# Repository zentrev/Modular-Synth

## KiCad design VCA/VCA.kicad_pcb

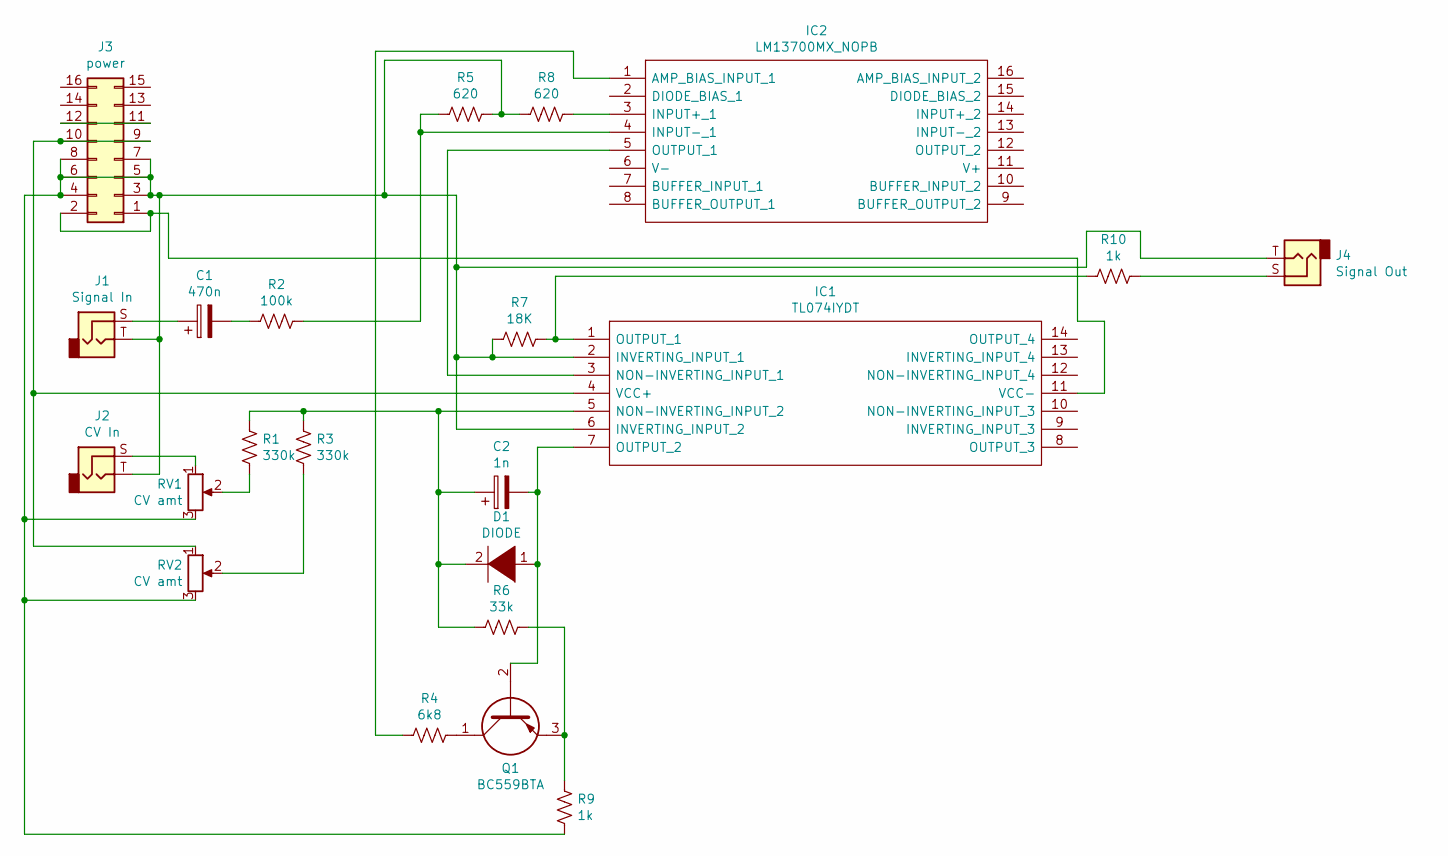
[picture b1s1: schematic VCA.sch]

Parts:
C1: 470n; CP_Radial_D4.0mm_P2.00mm
C2: 1n; CP_Radial_D4.0mm_P2.00mm
D1: DIODE; D_A-405_P2.54mm_Vertical_AnodeUp
IC1: TL074IYDT; SOIC127P600X175-14N; Mouser Part Number 511-TL074IYDT
IC2: LM13700MX_NOPB; SOIC127P600X175-16N; Mouser Part Number 926-LM13700MX/NOPB
J1: Signal In; Jack_3.5mm_CUI_SJ-3523-SMT_Horizontal
J2: CV In; Jack_3.5mm_CUI_SJ-3523-SMT_Horizontal
J3: power; IDC-Header_2x08_P2.54mm_Vertical
J4: Signal Out; Jack_3.5mm_CUI_SJ-3523-SMT_Horizontal
Q1: BC559BTA; TO-92_3L__AMMO_; Mouser Part Number 512-BC559BTA
R1, R3: 330k; R_Axial_DIN0204_L3.6mm_D1.6mm_P2.54mm_Vertical
R2: 100k; R_Axial_DIN0204_L3.6mm_D1.6mm_P2.54mm_Vertical
R4: 6k8; R_Axial_DIN0204_L3.6mm_D1.6mm_P2.54mm_Vertical
R5, R8: 620; R_Axial_DIN0204_L3.6mm_D1.6mm_P2.54mm_Vertical
R6: 33k; R_Axial_DIN0204_L3.6mm_D1.6mm_P2.54mm_Vertical
R7: 18K; R_Axial_DIN0204_L3.6mm_D1.6mm_P2.54mm_Vertical
R9, R10: 1k; R_Axial_DIN0204_L3.6mm_D1.6mm_P2.54mm_Vertical
RV1, RV2: CV amt; RK09D113BF25B15

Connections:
unnamed: C1.1, J1.S
unnamed: C1.2, R2.2
unnamed: C2.1, D1.2 (A), IC1.5 (NON-INVERTING_INPUT_2), R1.1, R3.1, R6.2
unnamed: C2.2, D1.1 (K), IC1.7 (OUTPUT_2), Q1.2
unnamed: IC1.1 (OUTPUT_1), R7.1, R10.2
unnamed: IC1.2 (INVERTING_INPUT_1), IC1.6 (INVERTING_INPUT_2), J1.T, J2.T, J3.3, J3.4, J3.5, J3.6, J3.7, J3.8, J4.T, R5.1, R7.2, R8.2, R9.2, RV1.3, RV2.3
unnamed: IC1.3 (NON-INVERTING_INPUT_1), IC2.5 (OUTPUT_1)
unnamed: IC1.4 (VCC+), J3.9, J3.10, RV2.1
unnamed: IC1.11 (VCC-), J3.1, J3.2
unnamed: IC2.1 (AMP_BIAS_INPUT_1), R4.2
unnamed: IC2.3 (INPUT+_1), R8.1
unnamed: IC2.4 (INPUT-_1), R2.1, R5.2
unnamed: J2.S, RV1.1
unnamed: J3.11, J3.12
unnamed: J4.S, R10.1
unnamed: Q1.1, R4.1
unnamed: Q1.3, R6.1, R9.1
unnamed: R1.2, RV1.2
unnamed: R3.2, RV2.2

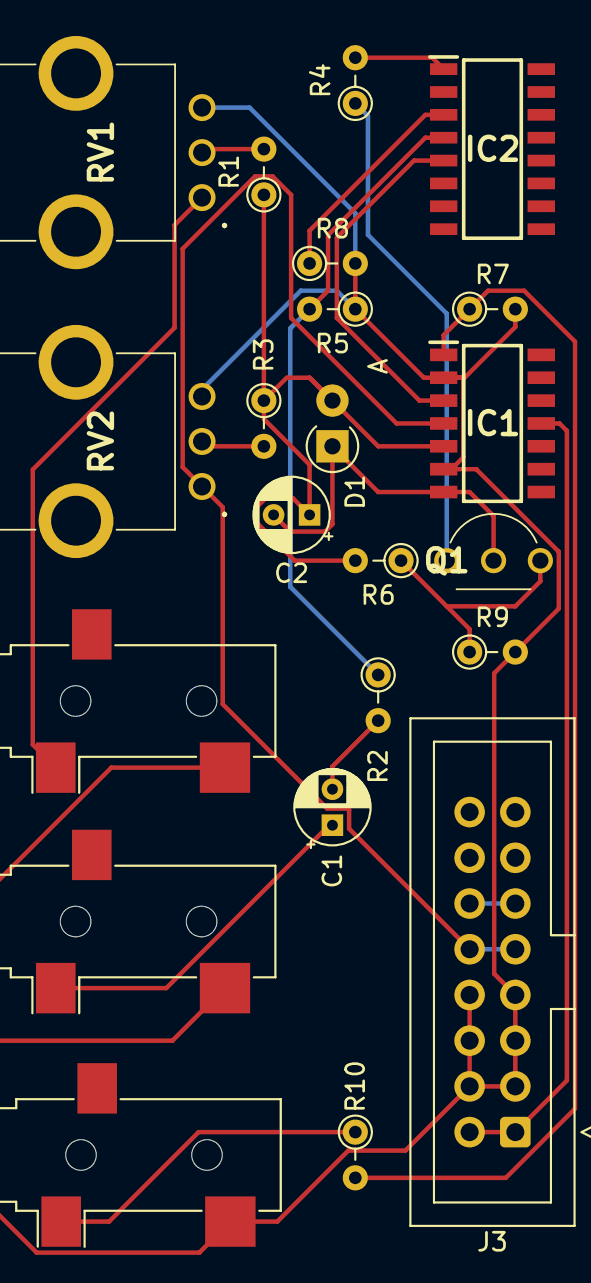
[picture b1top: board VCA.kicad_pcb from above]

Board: 2 copper layers, 22 parts (0 on the bottom side), 19 nets.

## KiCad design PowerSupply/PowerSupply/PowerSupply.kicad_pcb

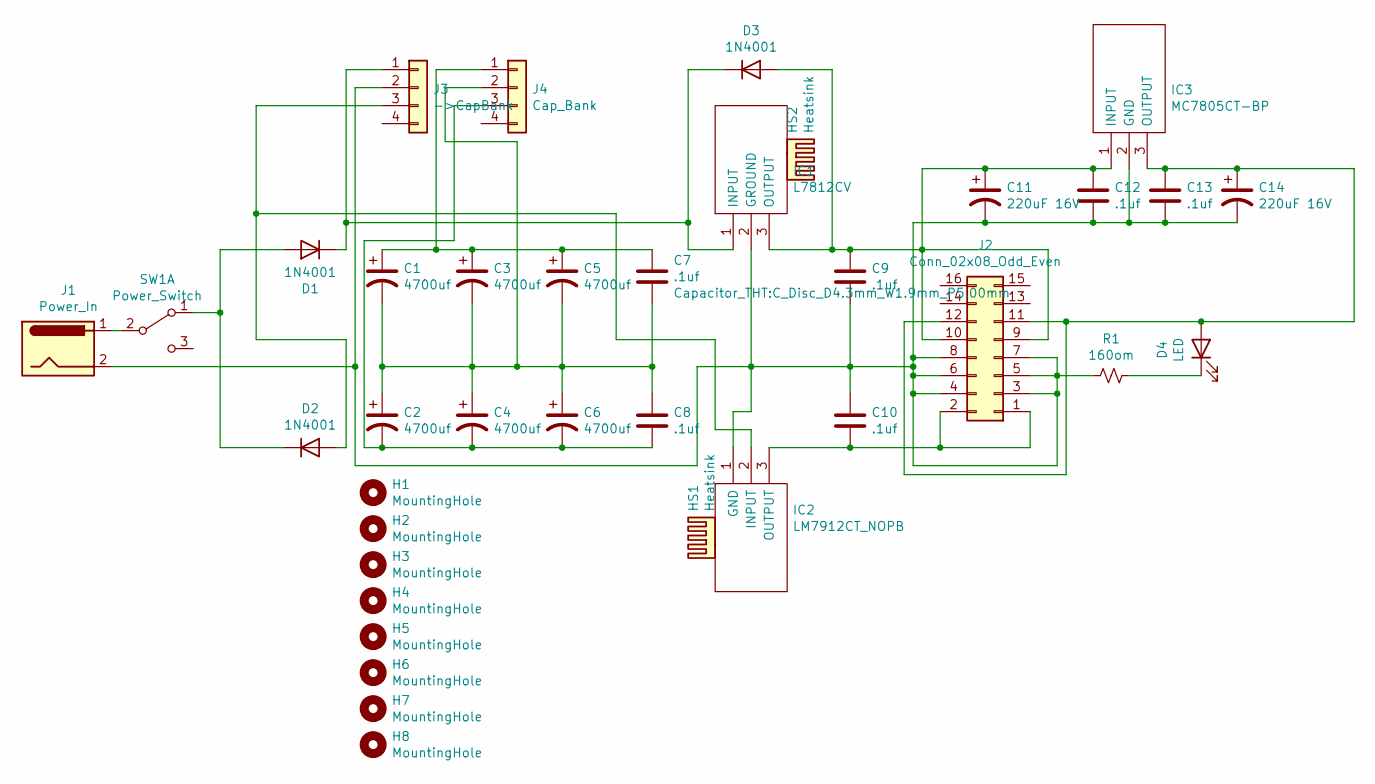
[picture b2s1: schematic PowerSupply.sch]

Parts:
C1, C2, C3, C4, C5, C6: 4700uf; CP_Radial_D18.0mm_P7.50mm
C7, C8, C9, C10, C12, C13: .1uf; C_Disc_D4.3mm_W1.9mm_P5.00mm
C11, C14: 220uF 16V; CP_Radial_D8.0mm_P3.50mm
D1, D2, D3: 1N4001; D_T-1_P5.08mm_Horizontal
D4: LED; LED_D1.8mm_W3.3mm_H2.4mm
H1, H2, H3, H4, H5, H6, H7, H8: MountingHole; MountingHole_2.5mm
HS1, HS2: Heatsink; Heatsink_Stonecold_HS-132_32x14mm_2xFixation1.5mm
IC1: L7812CV; TO255P460X1020X2008-3P; Mouser Part Number 511-L7812CV
IC2: LM7912CT_NOPB; TO254P470X1028X1955-3P; Mouser Part Number 926-LM7912CT/NOPB
IC3: MC7805CT-BP; TO254P482X1016X2325-3P; Mouser Part Number 833-MC7805CT-BP
J1: Power_In; BarrelJack_CLIFF_FC681465S_SMT_Horizontal
J2: Conn_02x08_Odd_Even; IDC-Header_2x08_P2.54mm_Vertical
J3: ->CapBank; PinHeader_1x04_P1.00mm_Vertical
J4: Cap_Bank; PinHeader_1x04_P1.00mm_Vertical
R1: 160om; R_Axial_DIN0207_L6.3mm_D2.5mm_P2.54mm_Vertical
SW1: Power_Switch; SW_SPDT_CK-JS102011SAQN

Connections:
unnamed: C1.1, C3.1, C5.1, C7.1, J4.1
unnamed: C1.2, C2.1, C3.2, C4.1, C5.2, C6.1, C7.2, C8.1, J4.2
unnamed: C2.2, C4.2, C6.2, C8.2, J4.3
unnamed: C9.2, C10.1, C11.2, C12.2, C13.2, C14.2, IC1.2 (GROUND), IC2.1 (GND), IC3.2 (GND), J1.2, J2.3, J2.4, J2.5, J2.6, J2.7, J2.8, J3.2, R1.1
unnamed: C10.2, IC2.3 (OUTPUT), J2.1, J2.2
unnamed: C9.1, C11.1, C12.1, D3.2 (A), IC1.3 (OUTPUT), IC3.1 (INPUT), J2.9, J2.10
unnamed: C13.1, C14.1, D4.2 (A), IC3.3 (OUTPUT), J2.11, J2.12
unnamed: D1.1 (K), D3.1 (K), IC1.1 (INPUT), J3.1
unnamed: D1.2 (A), D2.1 (K), SW1.1 (A)
unnamed: D2.2 (A), IC2.2 (INPUT), J3.3
unnamed: D4.1 (K), R1.2
unnamed: J1.1, SW1.2 (B)

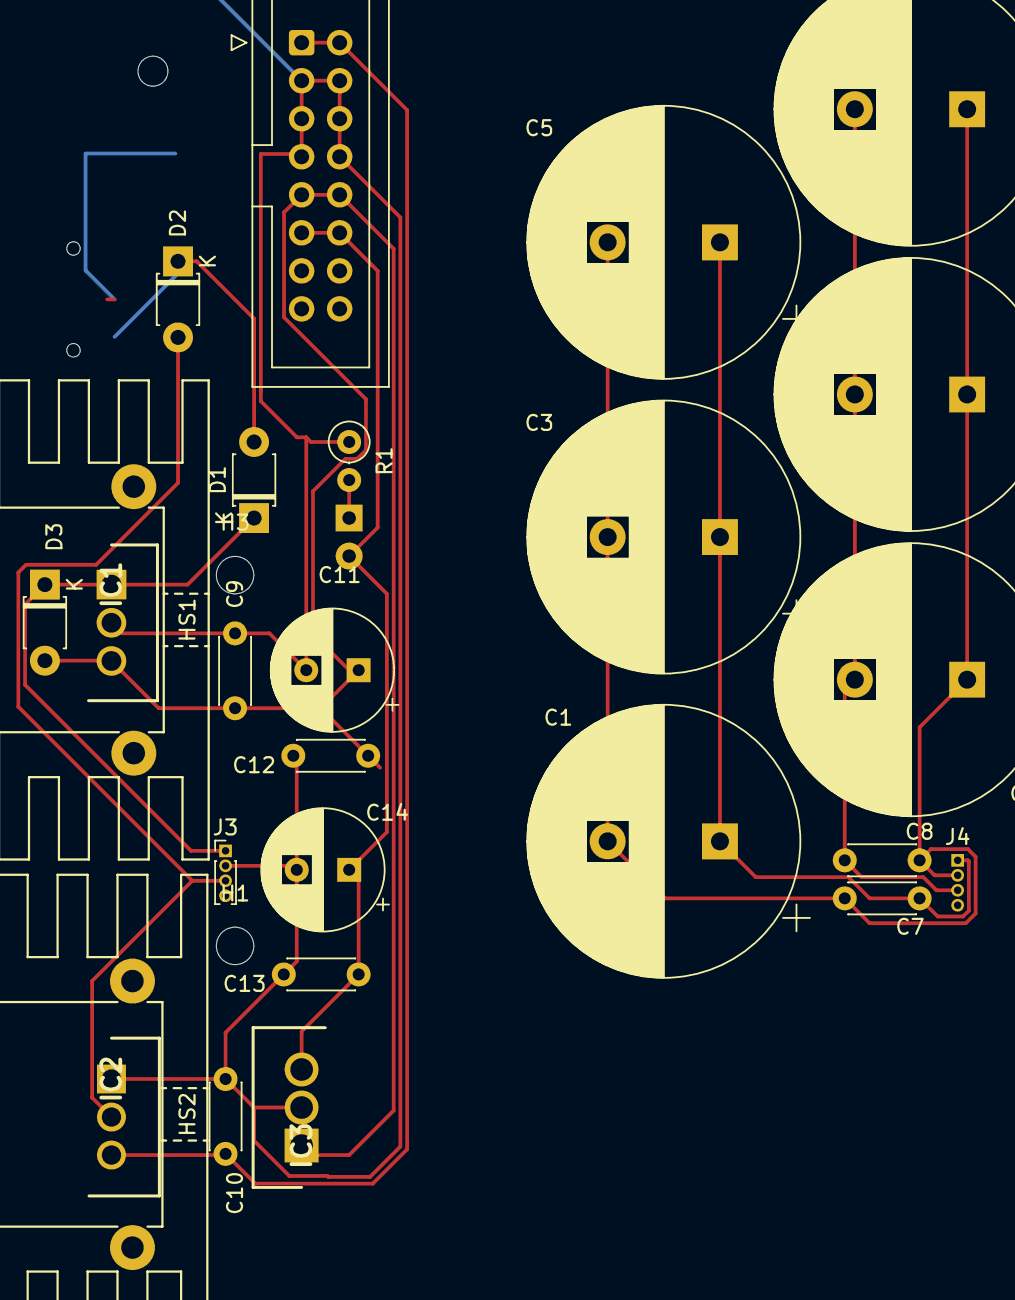
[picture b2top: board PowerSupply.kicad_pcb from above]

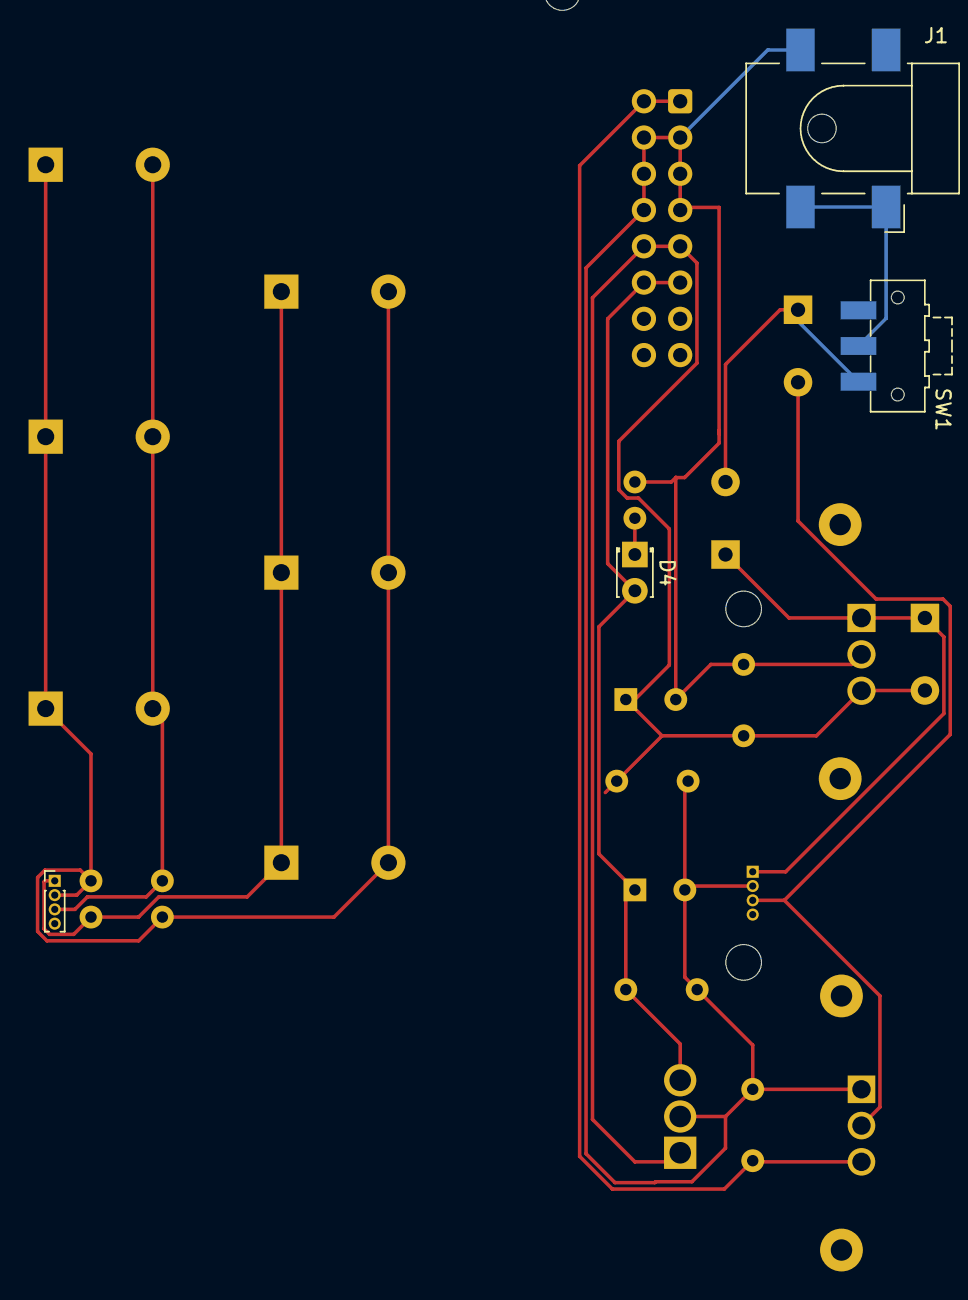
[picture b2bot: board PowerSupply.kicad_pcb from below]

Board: 2 copper layers, 37 parts (4 on the bottom side), 12 nets.

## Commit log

2021-03-16 Midi2CV info and circuit diagram
2021-03-16 removed unnecessary folder
2021-03-16 Updated Midi Info
2021-03-16 Updated Midi2CVInfo.txt
2021-03-17 Added VCO circuit and info
2021-03-17 Added Power Supply
2021-03-20 Added VCA
